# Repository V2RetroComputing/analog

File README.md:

# ∀2 Retro Computing Analog VGA Card & PicoPal

### Repo reorg
This repo is now the root of a multi-project tree.
Continue to use this repo to report issues with the hardware or firmware.

### Building the project files
Clone this repo and issue the following command to pull in the submodules
```
# git submodule update --init
```

The build.sh script in the analog-firmware project will build all the firmware variants.
If you wish to build a single variant, check the build.sh script for the syntax for the build folders.

When setting up a new card or upgrading from the older monolithic firmware, it is neccessary to use the flash preloader to format the configuration areas and install the fonts.  This only has to be done once, or if you want to restore the default fonts after uploading new ones.

### Sub-projects
[Flash Preloader](https://github.com/V2RetroComputing/analog-preload) |
[Firmware](https://github.com/V2RetroComputing/analog-firmware) |
[Utilities](https://github.com/V2RetroComputing/analog-utilities) |
[Hardware](https://github.com/V2RetroComputing/analog-hardware) |
[PicoPal V1](https://github.com/V2RetroComputing/picopal-v1)

### Acknowledgements
This is a fork of Mark Aikens [Apple II VGA](https://github.com/markadev/AppleII-VGA/) project with a new board design,
custom logic in an ATF16V8C to handle card select lines, and upgraded firmware with many new features.

Full details on purchasing and screenshots are available at [∀2 Retro Computing](https://www.v2retrocomputing.com/).

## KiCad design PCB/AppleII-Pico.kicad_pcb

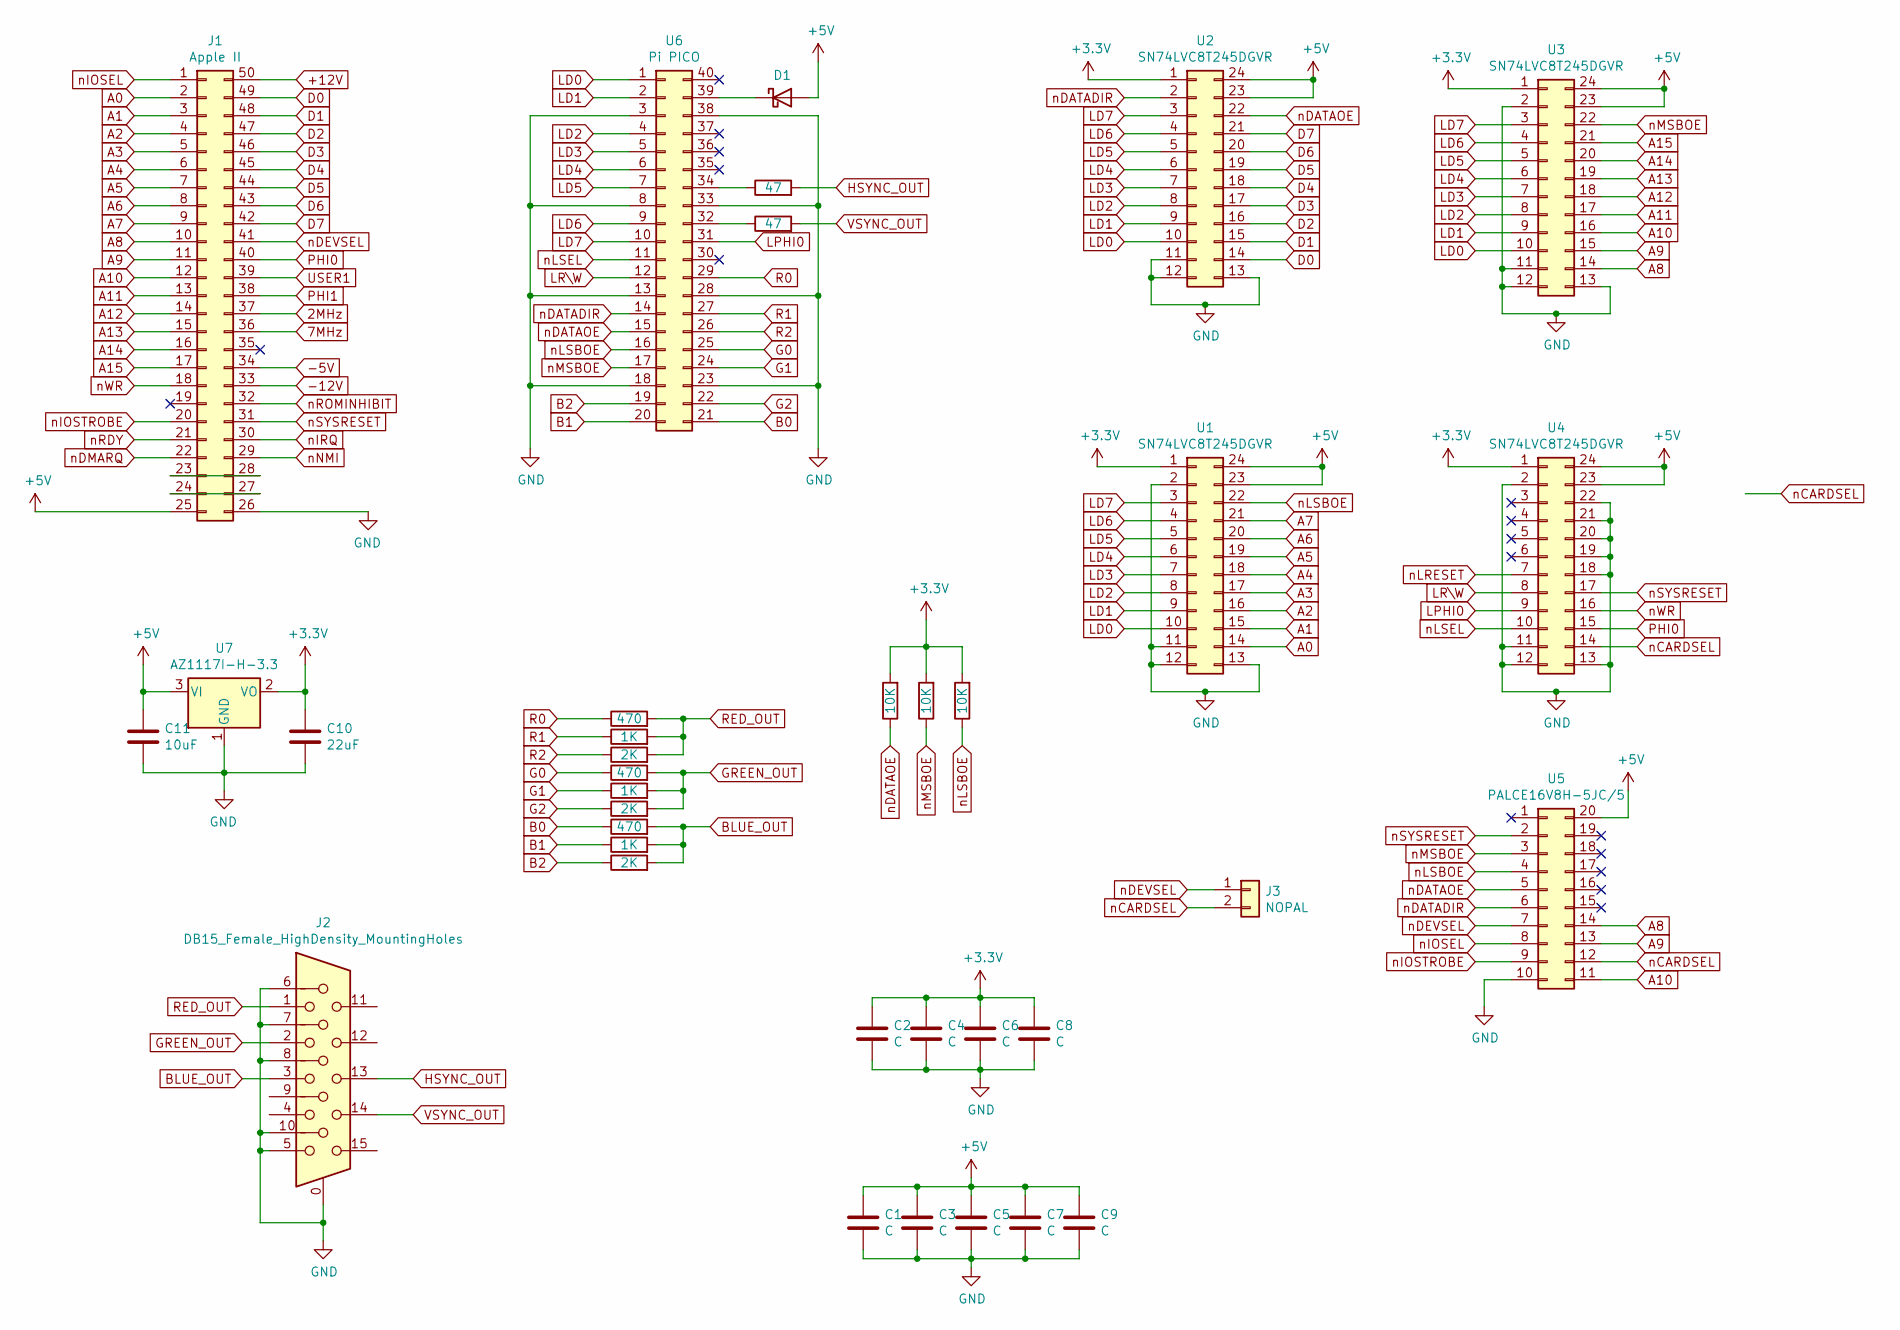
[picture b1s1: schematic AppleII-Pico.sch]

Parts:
C1, C2, C3, C4, C5, C6, C7, C8, C9: C; C_0402_1005Metric_Pad0.74x0.62mm_HandSolder
C10: 22uF; C_0805_2012Metric_Pad1.18x1.45mm_HandSolder
C11: 10uF; C_0805_2012Metric_Pad1.18x1.45mm_HandSolder
D1: D_Schottky; D_SMA_Handsoldering
J1: Apple II; AppleII
J2: DB15_Female_HighDensity_MountingHoles; DSUB-15-HD_Female_Horizontal_P2.29x1.98mm_EdgePinOffset3.03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
J3: NOPAL; SolderJumper-2_P1.3mm_Open_TrianglePad1.0x1.5mm
R1, R4, R7: 470; R_0402_1005Metric_Pad0.72x0.64mm_HandSolder
R2, R5, R8: 1K; R_0402_1005Metric_Pad0.72x0.64mm_HandSolder
R3, R6, R9: 2K; R_0402_1005Metric_Pad0.72x0.64mm_HandSolder
R10, R11: 47; R_0402_1005Metric_Pad0.72x0.64mm_HandSolder
R12, R13, R14: 10K; R_0402_1005Metric_Pad0.72x0.64mm_HandSolder
U1, U2, U3, U4: SN74LVC8T245DGVR; TSSOP-24_4.4x5mm_P0.4mm
U5: PALCE16V8H-5JC/5; PLCC-20
U6: Pi PICO; DIP-40_W16.51mm_SMDSocket_LongPads
U7: AZ1117I-H-3.3; SOT-223-3_TabPin2

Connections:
2MHz: J1.37
7MHz: J1.36
+3V3: C2.1, C4.1, C6.1, C8.1, C10.1, R12.2, R13.2, R14.2, U1.1, U2.1, U3.1, U4.1, U7.2 (VO)
+5V: C1.1, C3.1, C5.1, C7.1, C9.1, C11.1, D1.2 (A), J1.25, U1.23, U1.24, U2.23, U2.24, U3.23, U3.24, U4.23, U4.24, U5.20, U7.3 (VI)
+12V: J1.50
-5V: J1.34
-12V: J1.33
A0: J1.2, U1.14
A1: J1.3, U1.15
A2: J1.4, U1.16
A3: J1.5, U1.17
A4: J1.6, U1.18
A5: J1.7, U1.19
A6: J1.8, U1.20
A7: J1.9, U1.21
A8: J1.10, U3.14, U5.14
A9: J1.11, U3.15, U5.13
A10: J1.12, U3.16, U5.11
A11: J1.13, U3.17
A12: J1.14, U3.18
A13: J1.15, U3.19
A14: J1.16, U3.20
A15: J1.17, U3.21
B0: R7.1, U6.21
B1: R8.1, U6.20
B2: R9.1, U6.19
BLUE_OUT: J2.3, R7.2, R8.2, R9.2
D0: J1.49, U2.14
D1: J1.48, U2.15
D2: J1.47, U2.16
D3: J1.46, U2.17
D4: J1.45, U2.18
D5: J1.44, U2.19
D6: J1.43, U2.20
D7: J1.42, U2.21
G0: R4.1, U6.25
G1: R5.1, U6.24
G2: R6.1, U6.22
GND: C1.2, C2.2, C3.2, C4.2, C5.2, C6.2, C7.2, C8.2, C9.2, C10.2, C11.2, J1.26, J2.0, J2.5, J2.6, J2.7, J2.8, J2.10, U1.2, U1.11, U1.12, U1.13, U2.11, U2.12, U2.13, U3.2, U3.11, U3.12, U3.13, U4.2, U4.11, U4.12, U4.13, U4.18, U4.19, U4.20, U4.21, U4.22, U5.10, U6.3, U6.8, U6.13, U6.18, U6.23, U6.28, U6.33, U6.38, U7.1 (GND)
GREEN_OUT: J2.2, R4.2, R5.2, R6.2
HSYNC_OUT: J2.13, R10.2
LD0: U1.10, U2.10, U3.10, U6.1
LD1: U1.9, U2.9, U3.9, U6.2
LD2: U1.8, U2.8, U3.8, U6.4
LD3: U1.7, U2.7, U3.7, U6.5
LD4: U1.6, U2.6, U3.6, U6.6
LD5: U1.5, U2.5, U3.5, U6.7
LD6: U1.4, U2.4, U3.4, U6.9
LD7: U1.3, U2.3, U3.3, U6.10
LPHI0: U4.9, U6.31
LR\W: U4.8, U6.12
unnamed: D1.1 (K), U6.39
unnamed: J1.23, J1.28
unnamed: J1.24, J1.27
unnamed: R10.1, U6.34
unnamed: R11.1, U6.32
PHI0: J1.40, U4.15
PHI1: J1.38
R0: R1.1, U6.29
R1: R2.1, U6.27
R2: R3.1, U6.26
RED_OUT: J2.1, R1.2, R2.2, R3.2
USER1: J1.39
VSYNC_OUT: J2.14, R11.2
nCARDSEL: J3.2, U4.14, U5.12
nDATADIR: U2.2, U5.6, U6.14
nDATAOE: R12.1, U2.22, U5.5, U6.15
nDEVSEL: J1.41, J3.1, U5.7
nDMARQ: J1.22
nIOSEL: J1.1, U5.8
nIOSTROBE: J1.20, U5.9
nIRQ: J1.30
nLRESET: U4.7
nLSBOE: R14.1, U1.22, U5.4, U6.16
nLSEL: U4.10, U6.11
nMSBOE: R13.1, U3.22, U5.3, U6.17
nNMI: J1.29
nRDY: J1.21
nROMINHIBIT: J1.32
nSYSRESET: J1.31, U4.17, U5.2
nWR: J1.18, U4.16

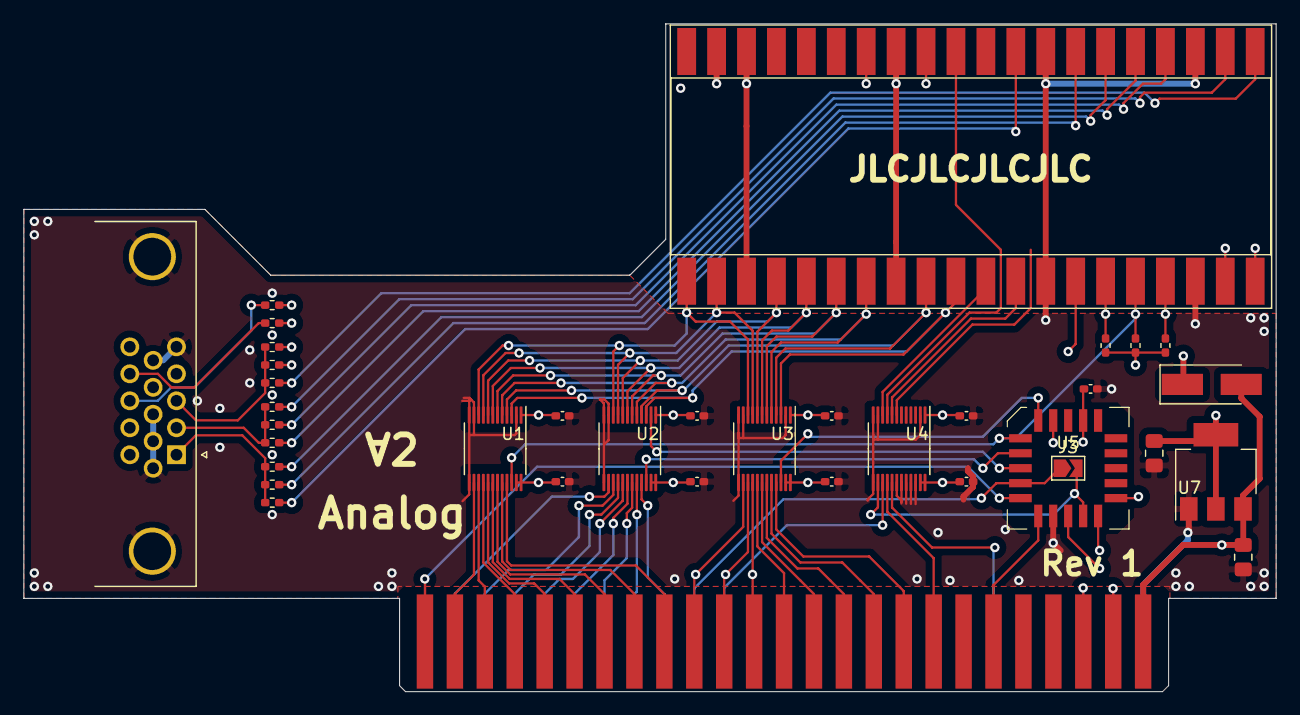
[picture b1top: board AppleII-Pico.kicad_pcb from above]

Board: 4 copper layers, 106.3 x 56.7 mm, 36 parts (0 on the bottom side), 68 nets.

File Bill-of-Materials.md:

|Qty|Designator|Item|Package|Description|
|---|---|---|---|---|
|9x|C1-C9|16V 100nF X7R|0402|Multilayer Ceramic Capacitor|
|1x|C11|25V 10uF X5R|0805|Multilayer Ceramic Capacitor|
|1x|C10|25V 22uF X5R|0805|Multilayer Ceramic Capacitor|
|1x|U7|AZ1117H-3.3|SOT-223|Fixed 3.3V regulator|
|1x|D1|SS14F|SMAF|40V 550mV @ 1A Shottkey Barrier Diode|
|3x|R12,R13,R14|10K Ohm 100mW|0402|10K Ohm 100mW Thin Film Resistor|
|3x|R3,R6,R9|2K Ohm 100mW|0402|2K Ohm 100mW Thin Film Resistor|
|3x|R2,R5,R8|1K Ohm 100mW|0402|1K Ohm 100mW Thin Film Resistor|
|3x|R1,R4,R7|470 Ohm 100mW|0402|470 Ohm 100mW Thin Film Resistor|
|2x|R10,R11|47 Ohm 100mW|0402|47 Ohm 100mW Thin Film Resistor|
|4x|U1-U4|SN74LVC8T245DGVR|TVSOP-24|Texas Instruments SN74LVC8T245DGVR Level Translating Transceiver|
|1x|U5|ATF16V8C-5JX|PLCC-20|Microchip ATF16V8C PLD|
|1x|U6|Pico-W|Module|Raspberry Pi Pico or Pico-W module (no pins)|
|1x|J2|VGA Connector|HD-15|High-Density D-SUB 15 VGA Connector|

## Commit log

2023-01-07 HW Rev 1, FW 2023-01-06-000
2023-01-07 Updated license
2023-01-07 Updated logo
2023-01-07 Added .gitignore
2023-01-08 RP2040 triggered $C800 release
    CUPL code had not been updated for HW Rev 1 which inverted the RP2040's data direction pin, which is used in concert with the level shifter select lines to trigger a release of the $C800 window from 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
2023-01-08 VGA mode bugfixes
    AUX page was being selected due to an errant && where a & should have been. IIe and IIgs registers were being written during read cycles.
2023-01-08 Remove unused flash programming stub
    Remove stubs for old flash programming method. New version uses a dedicated mode to allow access to littlefs from the Apple II.
2023-01-08 Diagnostic Mode
    MODE=DIAG allows testing the card addressing via the PicoPal chip.
2023-01-08 PicoPal logic fixes
    Simulation revealed errors in the CUPL logic regarding the $C800 window selection.
2023-01-09 $C800 Stability Fixes
2023-01-17 Firmware Release 23-01-16-119
    New autodetect routines for Apple II+, IIe (Platinum), IIgs (ROM03).
    Timing tweaks to improve compatibility on IIgs and IIe.
    Corrected text rendering on all supported machines.
    Initial Super HiRes support (not recommended to use at this time)
    Monochrome DHGR and HGR support activated with IIgs MONOCOLOR or NEWVID registers.
    80 Column mode on IIe and IIgs.
2023-01-29 Release 01-19-2023-131
2023-02-01 January 30, 2023 Beta Build
    Added machine types, character rom fixes, render code consolidation.
    DPMS Sleep mode when the RP2040 is powered separately from the Apple.
2023-02-01 Fix missing include
2023-03-02 Build 0159
    Progress on PCPI mode bug fixes. PCPI mode is now working again, but the config interface is still broken enough to prevent the use of the config utility while in this mode.. Sending the FORMAT comma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
    Replace n with the slot number the card is installed in:
    Correction of mousetext / inverse / flashing handling on IIe
    see https://github.com/V2RetroComputing/analog/issues/3
    ]CALL -151
    *CnF0:46 4F 52 4D 41 54 00 00
2023-03-02 Build 0159
    Progress on PCPI mode bug fixes. PCPI mode is now working again, but the config interface is still broken enough to prevent the use of the config utility while in this mode.. Sending the FORMAT comma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
    Replace n with the slot number the card is installed in:
    ]CALL -151
    *CnF0:46 4F 52 4D 41 54 00 00
    Correction of mousetext / inverse / flashing handling on IIe
    see https://github.com/V2RetroComputing/analog/issues/3
2023-03-02 Ignore build-lc folder
2023-04-17 Project files reorg
    Cleaning up the repos to break the project into smaller chunks.
2023-04-17 Update analog-hardware
2023-04-22 Update analog-utilites for 20230421 Utilities Update
2023-04-22 Updates for 20230421
2023-05-02 Update sub projects
2023-05-03 Update analog-firmware
2023-05-05 20230504 Release
